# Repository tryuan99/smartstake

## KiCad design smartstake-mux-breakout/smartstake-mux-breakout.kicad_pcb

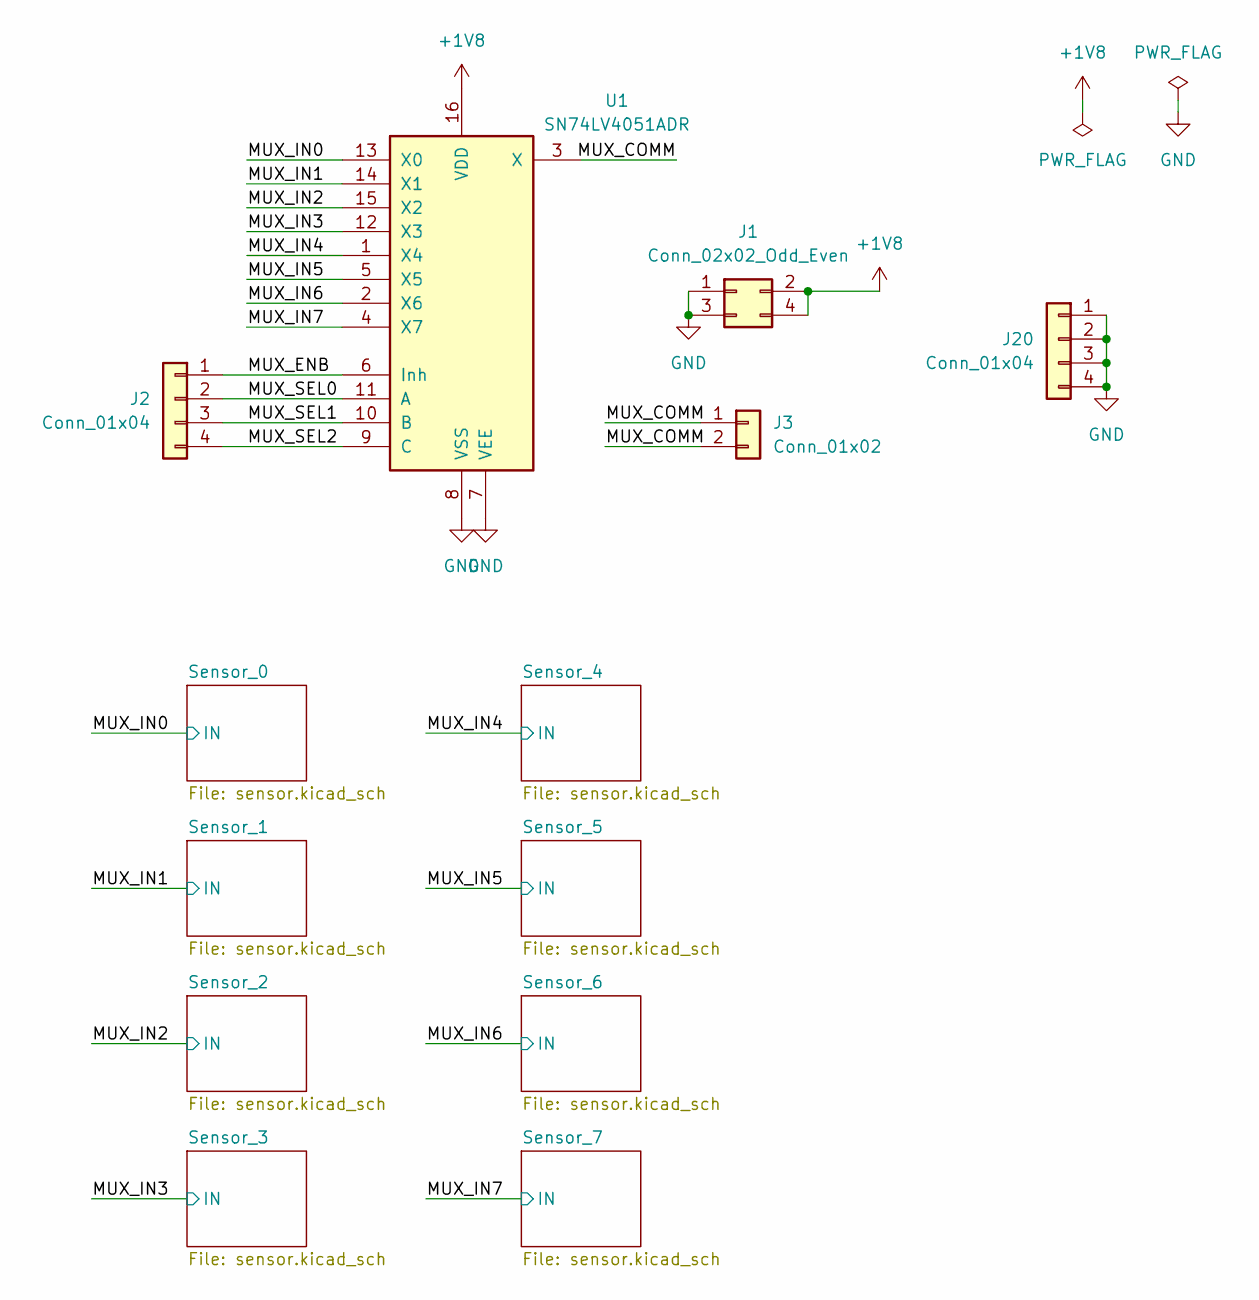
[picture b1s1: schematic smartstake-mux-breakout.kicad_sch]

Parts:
J1: Conn_02x02_Odd_Even; PinHeader_2x02_P2.54mm_Vertical
J2, J20: Conn_01x04; PinHeader_1x04_P2.54mm_Vertical
J3: Conn_01x02; PinHeader_1x02_P2.54mm_Vertical
U1: SN74LV4051ADR; SOIC-16_4.55x10.3mm_P1.27mm

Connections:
+1V8: J1.2, J1.4, U1.16 (VDD)
/MUX_COMM: J3.1, J3.2, U1.3 (X)
/MUX_ENB: J2.1, U1.6 (Inh)
/MUX_IN0: U1.13 (X0); also elsewhere on the board
/MUX_IN1: U1.14 (X1); also elsewhere on the board
/MUX_IN2: U1.15 (X2); also elsewhere on the board
/MUX_IN3: U1.12 (X3); also elsewhere on the board
/MUX_IN4: U1.1 (X4); also elsewhere on the board
/MUX_IN5: U1.5 (X5); also elsewhere on the board
/MUX_IN6: U1.2 (X6); also elsewhere on the board
/MUX_IN7: U1.4 (X7); also elsewhere on the board
/MUX_SEL0: J2.2, U1.11 (A)
/MUX_SEL1: J2.3, U1.10 (B)
/MUX_SEL2: J2.4, U1.9 (C)
GND: J1.1, J1.3, J20.1, J20.2, J20.3, J20.4, U1.7 (VEE), U1.8 (VSS); also elsewhere on the board

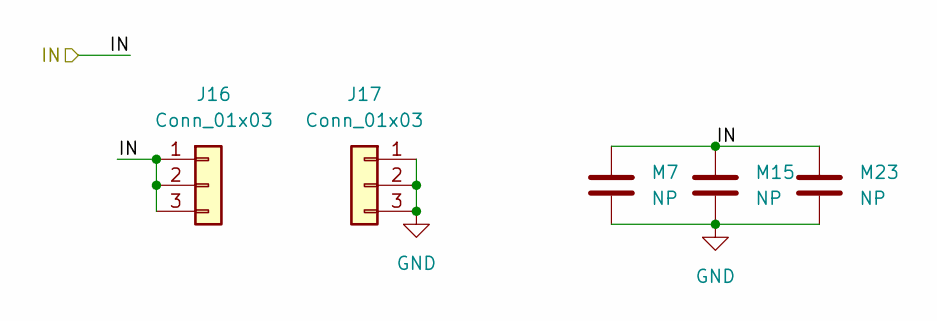
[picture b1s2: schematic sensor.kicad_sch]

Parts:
J16, J17: Conn_01x03; PinSocket_1x03_P2.54mm_Vertical
M7, M15, M23: NP; C_0805_2012Metric

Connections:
/MUX_IN6: J16.1, J16.2, J16.3, M7.1, M15.1, M23.1; also elsewhere on the board
GND: J17.1, J17.2, J17.3, M7.2, M15.2, M23.2; also elsewhere on the board

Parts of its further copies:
J4, J5, J6, J7, J8, J9, J10, J11, J12, J13, J14, J15, J18, J19: Conn_01x03; PinSocket_1x03_P2.54mm_Vertical
M1, M2, M3, M4, M5, M6, M8, M9, M10, M11, M12, M13, M14, M16, M17, M18, M19, M20, M21, M22, M24: NP; C_0805_2012Metric

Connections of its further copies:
/MUX_IN0: J4.1, J4.2, J4.3, M1.1, M9.1, M17.1; also elsewhere on the board
/MUX_IN1: J6.1, J6.2, J6.3, M2.1, M10.1, M18.1; also elsewhere on the board
/MUX_IN2: J8.1, J8.2, J8.3, M3.1, M11.1, M19.1; also elsewhere on the board
/MUX_IN3: J10.1, J10.2, J10.3, M4.1, M12.1, M20.1; also elsewhere on the board
/MUX_IN4: J12.1, J12.2, J12.3, M5.1, M13.1, M21.1; also elsewhere on the board
/MUX_IN5: J14.1, J14.2, J14.3, M6.1, M14.1, M22.1; also elsewhere on the board
/MUX_IN7: J18.1, J18.2, J18.3, M8.1, M16.1, M24.1; also elsewhere on the board
GND: J5.1, J5.2, J5.3, J7.1, J7.2, J7.3, J9.1, J9.2, J9.3, J11.1, J11.2, J11.3, J13.1, J13.2, J13.3, J15.1, J15.2, J15.3, J19.1, J19.2, J19.3, M1.2, M2.2, M3.2, M4.2, M5.2, M6.2, M8.2, M9.2, M10.2, M11.2, M12.2, M13.2, M14.2, M16.2, M17.2, M18.2, M19.2, M20.2, M21.2, M22.2, M24.2; also elsewhere on the board

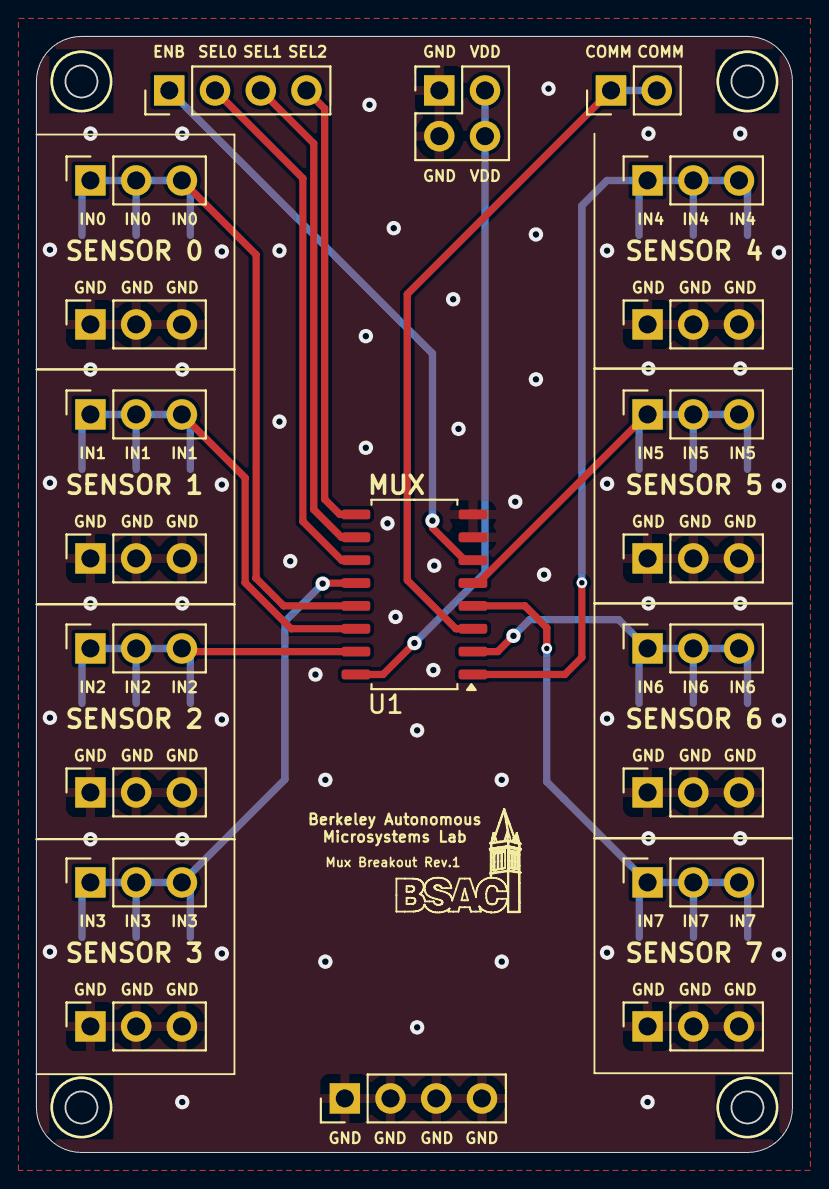
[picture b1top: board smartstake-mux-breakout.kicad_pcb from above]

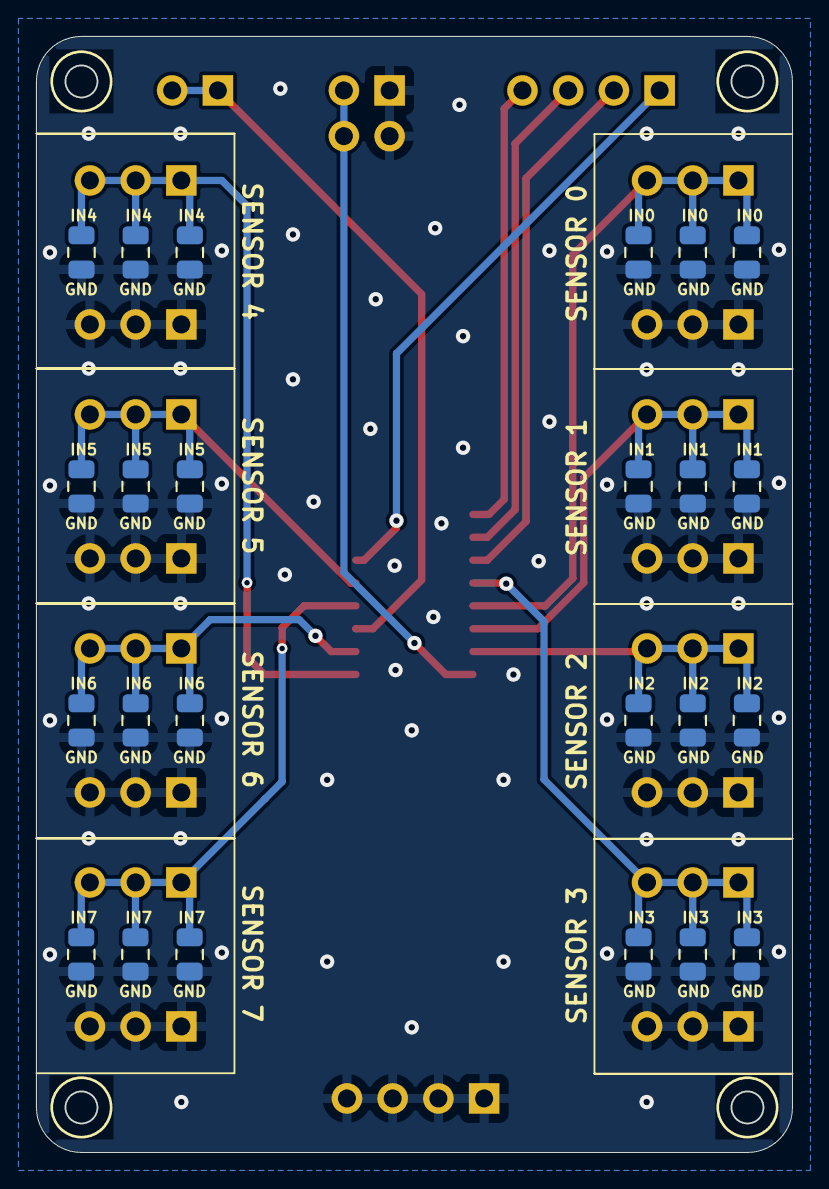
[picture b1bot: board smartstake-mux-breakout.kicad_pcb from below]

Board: 2 copper layers, 42.0 x 62.0 mm, 45 parts (24 on the bottom side), 15 nets.

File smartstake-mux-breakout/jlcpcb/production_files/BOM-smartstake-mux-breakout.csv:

Comment,Designator,Footprint,LCSC
Conn_01x02,J3,PinHeader_1x02_P2.54mm_Vertical,C124375
SN74LV4051ADR,U1,SOIC-16_4.55x10.3mm_P1.27mm,C128414
Conn_01x03,"J10,J11,J12,J13,J14,J15,J16,J17,J18,J19,J4,J5,J6,J7,J8,J9",PinSocket_1x03_P2.54mm_Vertical,C146243
Conn_01x04,"J2,J20",PinHeader_1x04_P2.54mm_Vertical,C5116483
Conn_02x02_Odd_Even,J1,PinHeader_2x02_P2.54mm_Vertical,C66690
NP,M21,C_0805_2012Metric,
NP,M12,C_0805_2012Metric,
NP,M23,C_0805_2012Metric,
NP,M10,C_0805_2012Metric,
NP,M20,C_0805_2012Metric,
NP,M9,C_0805_2012Metric,
NP,M13,C_0805_2012Metric,
NP,M19,C_0805_2012Metric,
NP,M14,C_0805_2012Metric,
NP,M2,C_0805_2012Metric,
NP,M4,C_0805_2012Metric,
NP,M22,C_0805_2012Metric,
NP,M16,C_0805_2012Metric,
NP,M18,C_0805_2012Metric,
NP,M6,C_0805_2012Metric,
NP,M11,C_0805_2012Metric,
NP,M7,C_0805_2012Metric,
NP,M15,C_0805_2012Metric,
NP,M24,C_0805_2012Metric,
NP,M17,C_0805_2012Metric,
NP,M5,C_0805_2012Metric,
NP,M8,C_0805_2012Metric,
NP,M3,C_0805_2012Metric,
NP,M1,C_0805_2012Metric,

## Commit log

2024-06-28 Add README.md
2024-06-28 Add mux breakout board rev. 1
